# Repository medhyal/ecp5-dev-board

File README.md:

# ecp5-dev-board
ECP5 FPGA DEV BOARD

Lattice LFE5U-12F FPGA  
Built in FTDI FT2232H Programmer

Errata:  
Q1 - wrong footprint

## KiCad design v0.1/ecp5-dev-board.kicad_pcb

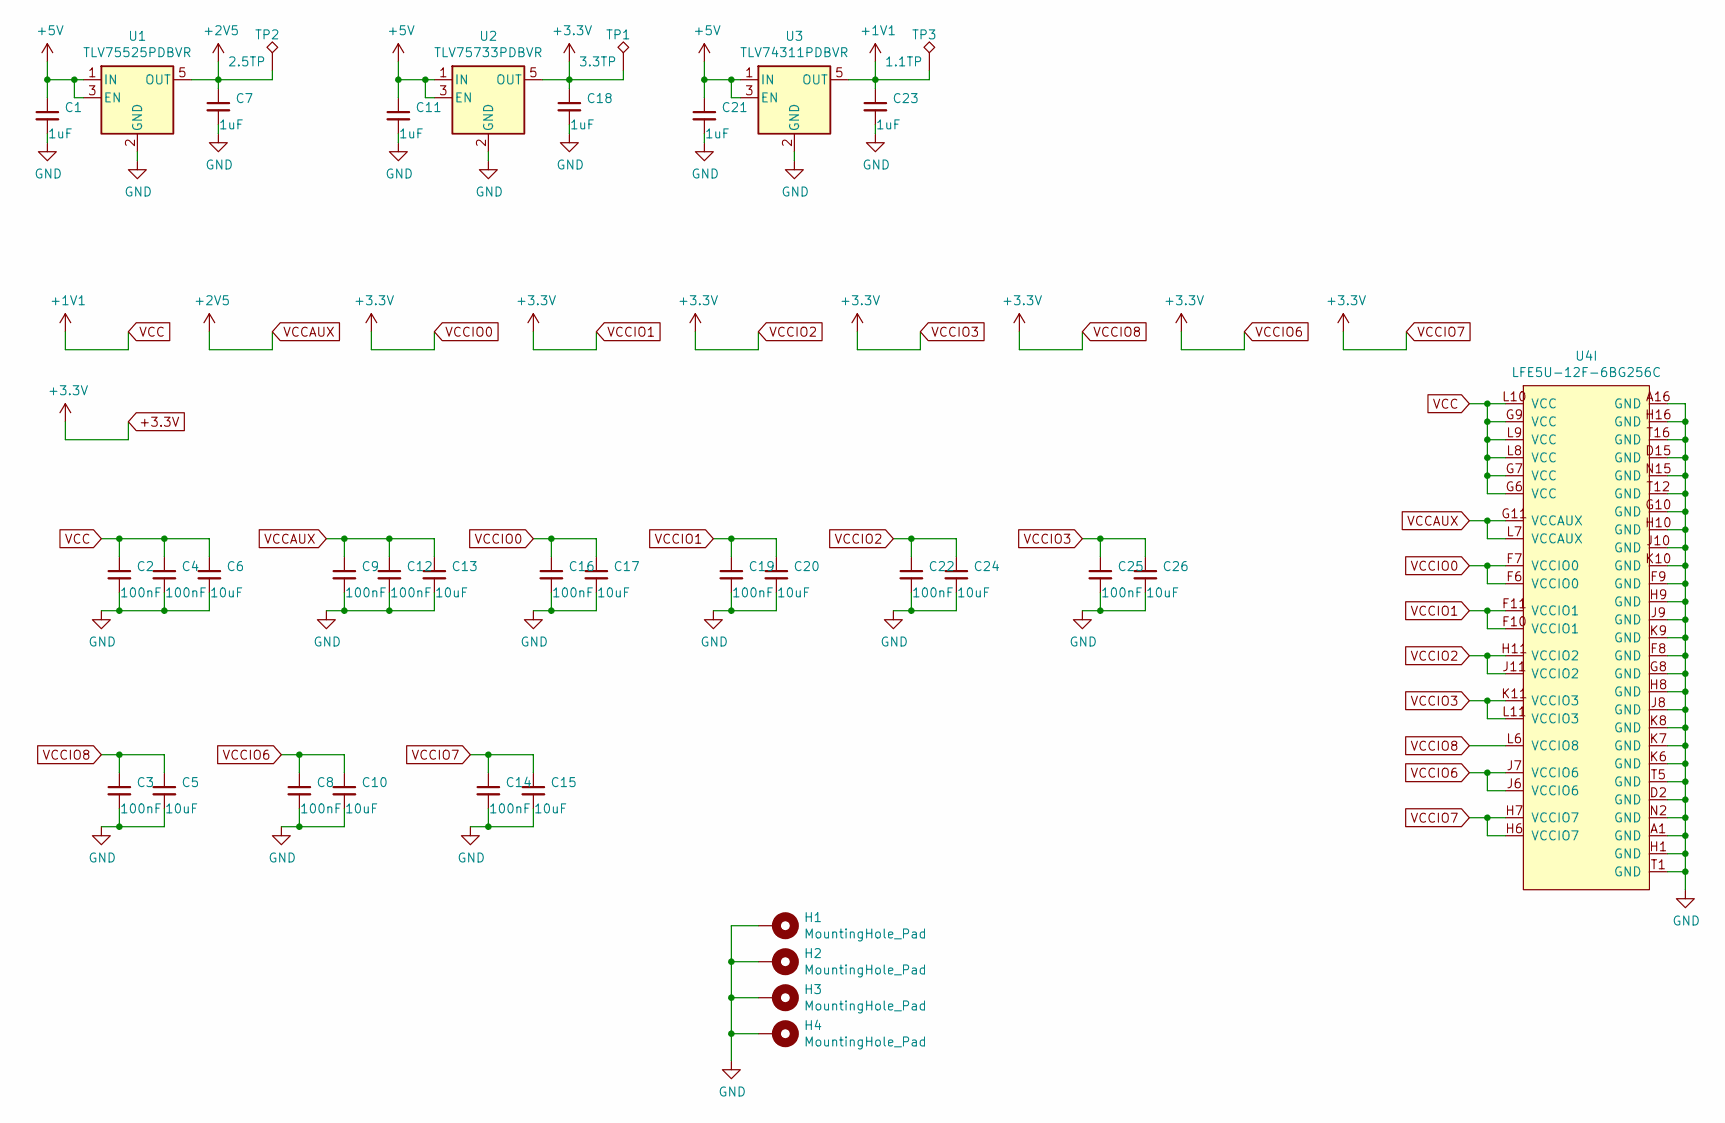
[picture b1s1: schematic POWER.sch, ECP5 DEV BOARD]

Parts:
C1, C7, C11, C18, C21, C23: 1uF; C_0603_1608Metric
C2, C3, C4, C8, C9, C12, C14, C16, C19, C22, C25: 100nF; C_0402_1005Metric
C5, C6, C10, C13, C15, C17, C20, C24, C26: 10uF; C_0402_1005Metric
H1, H2, H3, H4: MountingHole_Pad; MountingHole_3.2mm_M3_ISO14580_Pad
TP1: 3.3TP; TestPoint_Pad_D1.0mm
TP2: 2.5TP; TestPoint_Pad_D1.0mm
TP3: 1.1TP; TestPoint_Pad_D1.0mm
U1: TLV75525PDBVR; SOT-23-5
U2: TLV75733PDBVR; SOT-23-5
U3: TLV74311PDBVR; SOT-23-5
U4: LFE5U-12F-6BG256C; BGA-256_14.0x14.0mm_Layout16x16_P0.8mm_Ball0.45mm_Pad0.32mm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

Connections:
+3.3V: C3.1, C5.1, C8.1, C10.1, C14.1, C15.1, C16.1, C17.1, C18.1, C19.1, C20.1, C22.1, C24.1, C25.1, C26.1, TP1.1, U2.5 (OUT), U4.F6 (VCCIO0), U4.F7 (VCCIO0), U4.F10 (VCCIO1), U4.F11 (VCCIO1), U4.H6 (VCCIO7), U4.H7 (VCCIO7), U4.H11 (VCCIO2), U4.J6 (VCCIO6), U4.J7 (VCCIO6), U4.J11 (VCCIO2), U4.K11 (VCCIO3), U4.L6 (VCCIO8), U4.L11 (VCCIO3); also elsewhere on the board
+5V: C1.1, C11.1, C21.1, U1.1 (IN), U1.3 (EN), U2.1 (IN), U2.3 (EN), U3.1 (IN), U3.3 (EN); also elsewhere on the board
VCC: C2.1, C4.1, C6.1, C23.1, TP3.1, U3.5 (OUT), U4.G6 (VCC), U4.G7 (VCC), U4.G9 (VCC), U4.L8 (VCC), U4.L9 (VCC), U4.L10 (VCC)
VCCAUX: C7.1, C9.1, C12.1, C13.1, TP2.1, U1.5 (OUT), U4.G11 (VCCAUX), U4.L7 (VCCAUX)

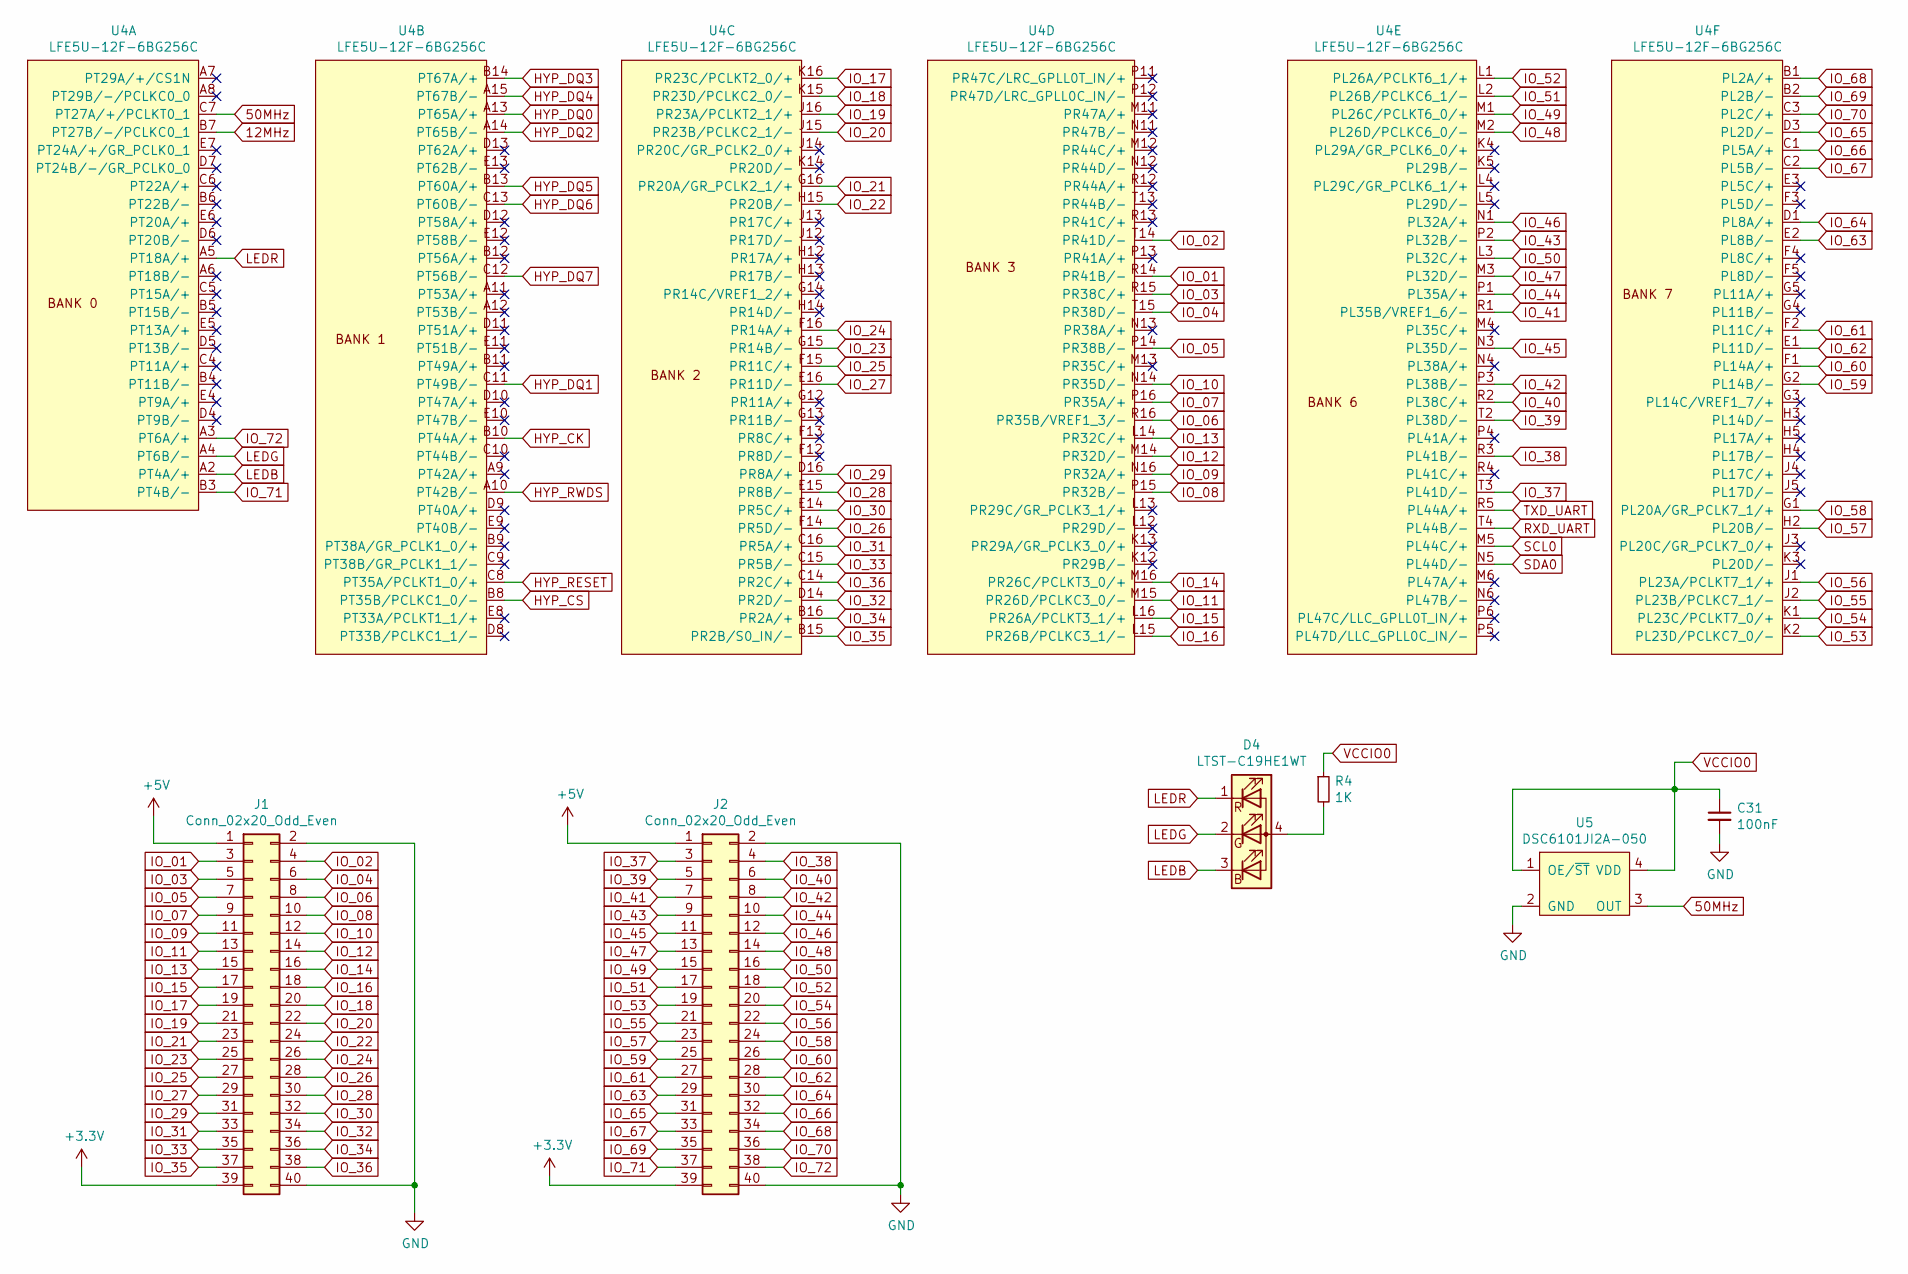
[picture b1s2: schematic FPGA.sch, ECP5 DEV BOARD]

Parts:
C31: 100nF; C_0402_1005Metric
D4: ‎LTST-C19HE1WT‎; LED_LiteOn_LTST-C19HE1WT
J1, J2: Conn_02x20_Odd_Even; PinHeader_2x20_P2.54mm_Vertical
R4: 1K; R_0402_1005Metric
U4: LFE5U-12F-6BG256C; BGA-256_14.0x14.0mm_Layout16x16_P0.8mm_Ball0.45mm_Pad0.32mm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
U5: DSC6101JI2A-050; DSC6101JI2A-012

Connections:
12MHz: U4.B7 (PT27B/-/PCLKC0_1); also elsewhere on the board
50MHz: U4.C7 (PT27A/+/PCLKT0_1), U5.3 (OUT)
+3.3V: C31.1, J1.39, J2.39, R4.1, U5.1 (OE/~ST), U5.4 (VDD); also elsewhere on the board
+5V: J1.1, J2.1; also elsewhere on the board
HYP_CK: U4.B10 (PT44A/+); also elsewhere on the board
HYP_CS: U4.B8 (PT35B/PCLKC1_0/-); also elsewhere on the board
HYP_DQ0: U4.A13 (PT65A/+); also elsewhere on the board
HYP_DQ1: U4.C11 (PT49B/-); also elsewhere on the board
HYP_DQ2: U4.A14 (PT65B/-); also elsewhere on the board
HYP_DQ3: U4.B14 (PT67A/+); also elsewhere on the board
HYP_DQ4: U4.A15 (PT67B/-); also elsewhere on the board
HYP_DQ5: U4.B13 (PT60A/+); also elsewhere on the board
HYP_DQ6: U4.C13 (PT60B/-); also elsewhere on the board
HYP_DQ7: U4.C12 (PT56B/-); also elsewhere on the board
HYP_RESET: U4.C8 (PT35A/PCLKT1_0/+); also elsewhere on the board
HYP_RWDS: U4.A10 (PT42B/-); also elsewhere on the board
IO_01: J1.3, U4.R14 (PR41B/-)
IO_02: J1.4, U4.T14 (PR41D/-)
IO_03: J1.5, U4.R15 (PR38C/+)
IO_04: J1.6, U4.T15 (PR38D/-)
IO_05: J1.7, U4.P14 (PR38B/-)
IO_06: J1.8, U4.R16 (PR35B/VREF1_3/-)
IO_07: J1.9, U4.P16 (PR35A/+)
IO_08: J1.10, U4.P15 (PR32B/-)
IO_09: J1.11, U4.N16 (PR32A/+)
IO_10: J1.12, U4.N14 (PR35D/-)
IO_11: J1.13, U4.M15 (PR26D/PCLKC3_0/-)
IO_12: J1.14, U4.M14 (PR32D/-)
IO_13: J1.15, U4.L14 (PR32C/+)
IO_14: J1.16, U4.M16 (PR26C/PCLKT3_0/+)
IO_15: J1.17, U4.L16 (PR26A/PCLKT3_1/+)
IO_16: J1.18, U4.L15 (PR26B/PCLKC3_1/-)
IO_17: J1.19, U4.K16 (PR23C/PCLKT2_0/+)
IO_18: J1.20, U4.K15 (PR23D/PCLKC2_0/-)
IO_19: J1.21, U4.J16 (PR23A/PCLKT2_1/+)
IO_20: J1.22, U4.J15 (PR23B/PCLKC2_1/-)
IO_21: J1.23, U4.G16 (PR20A/GR_PCLK2_1/+)
IO_22: J1.24, U4.H15 (PR20B/-)
IO_23: J1.25, U4.G15 (PR14B/-)
IO_24: J1.26, U4.F16 (PR14A/+)
IO_25: J1.27, U4.F15 (PR11C/+)
IO_26: J1.28, U4.F14 (PR5D/-)
IO_27: J1.29, U4.E16 (PR11D/-)
IO_28: J1.30, U4.E15 (PR8B/-)
IO_29: J1.31, U4.D16 (PR8A/+)
IO_30: J1.32, U4.E14 (PR5C/+)
IO_31: J1.33, U4.C16 (PR5A/+)
IO_32: J1.34, U4.D14 (PR2D/-)
IO_33: J1.35, U4.C15 (PR5B/-)
IO_34: J1.36, U4.B16 (PR2A/+)
IO_35: J1.37, U4.B15 (PR2B/S0_IN/-)
IO_36: J1.38, U4.C14 (PR2C/+)
IO_37: J2.3, U4.T3 (PL41D/-)
IO_38: J2.4, U4.R3 (PL41B/-)
IO_39: J2.5, U4.T2 (PL38D/-)
IO_40: J2.6, U4.R2 (PL38C/+)
IO_41: J2.7, U4.R1 (PL35B/VREF1_6/-)
IO_42: J2.8, U4.P3 (PL38B/-)
IO_43: J2.9, U4.P2 (PL32B/-)
IO_44: J2.10, U4.P1 (PL35A/+)
IO_45: J2.11, U4.N3 (PL35D/-)
IO_46: J2.12, U4.N1 (PL32A/+)
IO_47: J2.13, U4.M3 (PL32D/-)
IO_48: J2.14, U4.M2 (PL26D/PCLKC6_0/-)
IO_49: J2.15, U4.M1 (PL26C/PCLKT6_0/+)
IO_50: J2.16, U4.L3 (PL32C/+)
IO_51: J2.17, U4.L2 (PL26B/PCLKC6_1/-)
IO_52: J2.18, U4.L1 (PL26A/PCLKT6_1/+)
IO_53: J2.19, U4.K2 (PL23D/PCLKC7_0/-)
IO_54: J2.20, U4.K1 (PL23C/PCLKT7_0/+)
IO_55: J2.21, U4.J2 (PL23B/PCLKC7_1/-)
IO_56: J2.22, U4.J1 (PL23A/PCLKT7_1/+)
IO_57: J2.23, U4.H2 (PL20B/-)
IO_58: J2.24, U4.G1 (PL20A/GR_PCLK7_1/+)
IO_59: J2.25, U4.G2 (PL14B/-)
IO_60: J2.26, U4.F1 (PL14A/+)
IO_61: J2.27, U4.F2 (PL11C/+)
IO_62: J2.28, U4.E1 (PL11D/-)
IO_63: J2.29, U4.E2 (PL8B/-)
IO_64: J2.30, U4.D1 (PL8A/+)
IO_65: J2.31, U4.D3 (PL2D/-)
IO_66: J2.32, U4.C1 (PL5A/+)
IO_67: J2.33, U4.C2 (PL5B/-)
IO_68: J2.34, U4.B1 (PL2A/+)
IO_69: J2.35, U4.B2 (PL2B/-)
IO_70: J2.36, U4.C3 (PL2C/+)
IO_71: J2.37, U4.B3 (PT4B/-)
IO_72: J2.38, U4.A3 (PT6A/+)
LEDB: D4.3 (BK), U4.A2 (PT4A/+)
LEDG: D4.2 (GK), U4.A4 (PT6B/-)
LEDR: D4.1 (RK), U4.A5 (PT18A/+)
unnamed: D4.4 (A), R4.2
RXD_UART: U4.N5 (PL44D/-), U4.T4 (PL44B/-); also elsewhere on the board
SCL0: U4.M5 (PL44C/+), U4.R5 (PL44A/+); also elsewhere on the board

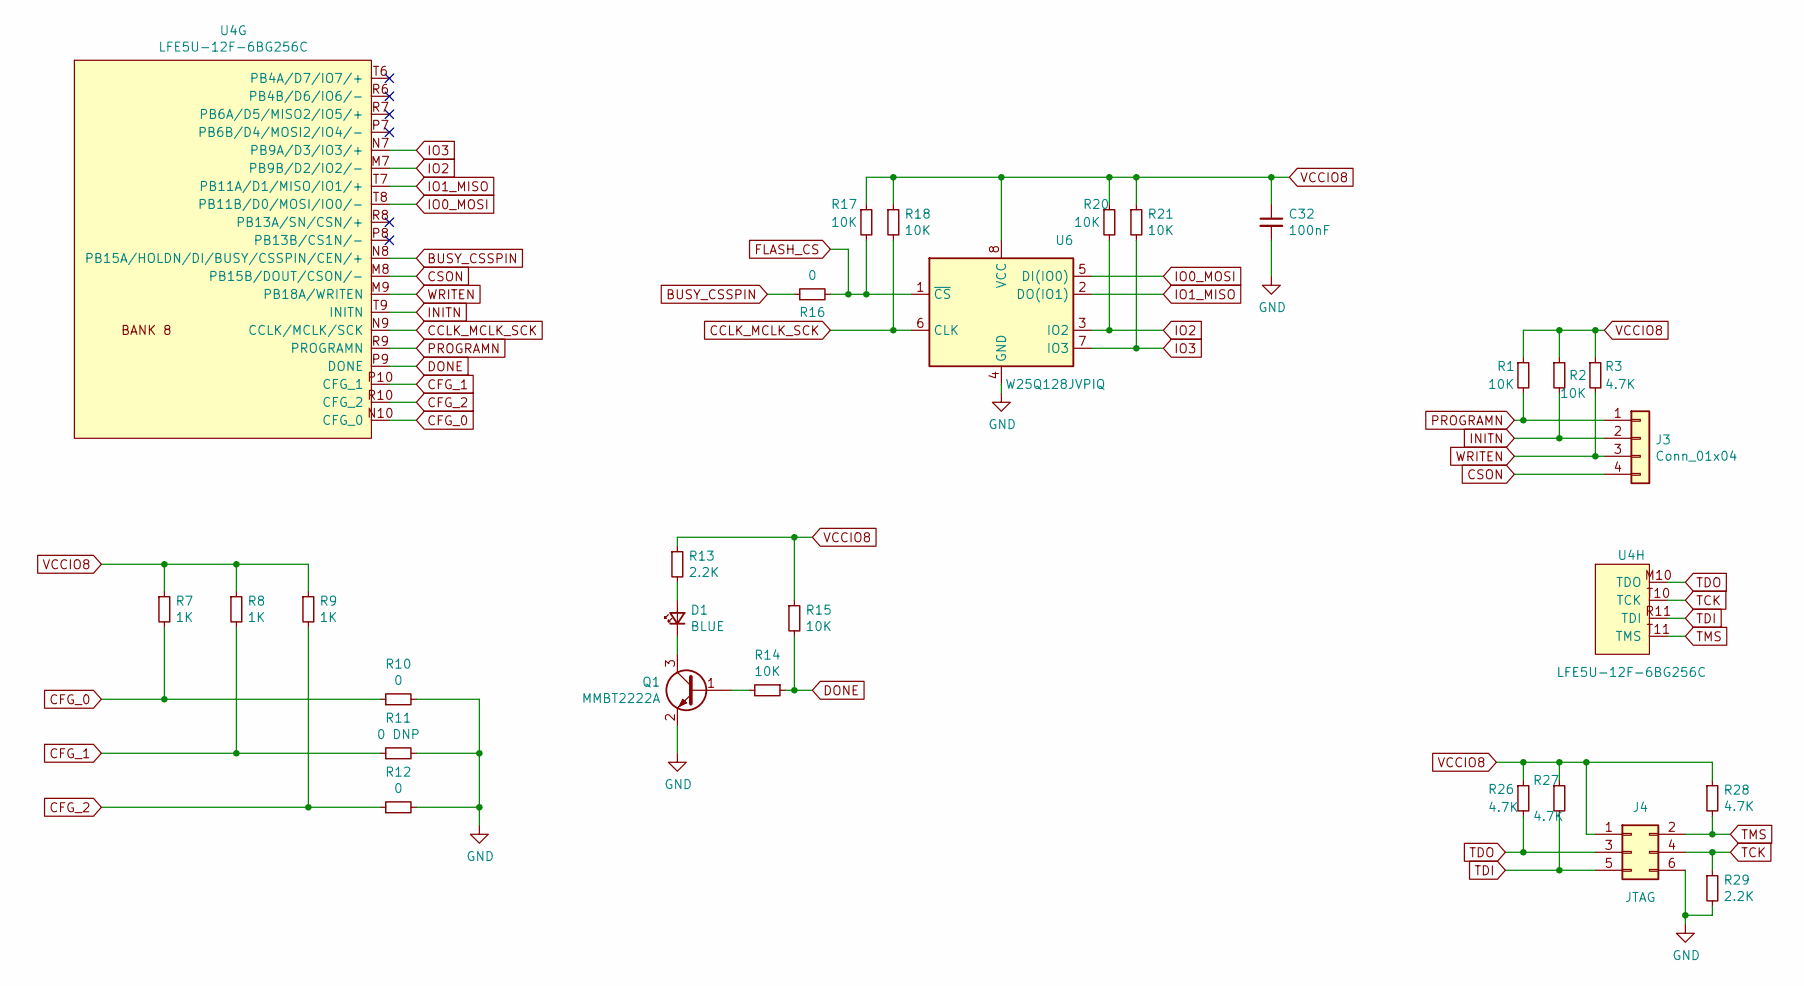
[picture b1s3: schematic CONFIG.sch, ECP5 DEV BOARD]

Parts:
C32: 100nF; C_0402_1005Metric
D1: BLUE; LED_0603_1608Metric
J3: Conn_01x04; PinHeader_1x04_P2.54mm_Vertical
J4: JTAG; PinHeader_2x03_P2.54mm_Vertical
Q1: MMBT2222A; SOT-23
R1, R2, R14, R15, R17, R18, R20, R21: 10K; R_0402_1005Metric
R3, R26, R27, R28: 4.7K; R_0402_1005Metric
R7, R8, R9: 1K; R_0402_1005Metric
R10, R12, R16: 0; R_0402_1005Metric
R11: 0 DNP; R_0402_1005Metric
R13, R29: 2.2K; R_0402_1005Metric
U4: LFE5U-12F-6BG256C; BGA-256_14.0x14.0mm_Layout16x16_P0.8mm_Ball0.45mm_Pad0.32mm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
U6: W25Q128JVPIQ; WSON-8-1EP_6x5mm_P1.27mm_EP3.4x4.3mm

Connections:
+3.3V: C32.1, J4.1, R1.1, R2.1, R3.1, R7.1, R8.1, R9.1, R13.1, R15.1, R17.1, R18.1, R20.1, R21.1, R26.1, R27.1, R28.1, U6.8 (VCC); also elsewhere on the board
BUSY_CSSPIN: R16.1, U4.N8 (PB15A/HOLDN/DI/BUSY/CSSPIN/CEN/+)
CCLK_MCLK_SCK: R18.2, U4.N9 (CCLK/MCLK/SCK), U6.6 (CLK)
CFG_0: R7.2, R10.1, U4.N10 (CFG_0)
CFG_1: R8.2, R11.1, U4.P10 (CFG_1)
CFG_2: R9.2, R12.1, U4.R10 (CFG_2)
CSON: J3.4, U4.M8 (PB15B/DOUT/CSON/-)
DONE: R14.1, R15.2, U4.P9 (DONE)
FLASH_CS: R16.2, R17.2, U6.1 (~CS)
INITN: J3.2, R2.2, U4.T9 (INITN)
IO0_MOSI: U4.T8 (PB11B/D0/MOSI/IO0/-), U6.5 (DI(IO0))
IO1_MISO: U4.T7 (PB11A/D1/MISO/IO1/+), U6.2 (DO(IO1))
IO2: R20.2, U4.M7 (PB9B/D2/IO2/-), U6.3 (IO2)
IO3: R21.2, U4.N7 (PB9A/D3/IO3/+), U6.7 (IO3)
unnamed: D1.1 (K), Q1.3 (C)
unnamed: D1.2 (A), R13.2
PROGRAMN: J3.1, R1.2, U4.R9 (PROGRAMN)
TCK: J4.4, R29.1, U4.T10 (TCK); also elsewhere on the board
TDI: J4.5, R27.2, U4.R11 (TDI); also elsewhere on the board
TDO: J4.3, R26.2, U4.M10 (TDO); also elsewhere on the board
TMS: J4.2, R28.2, U4.T11 (TMS); also elsewhere on the board
WRITEN: J3.3, R3.2, U4.M9 (PB18A/WRITEN)

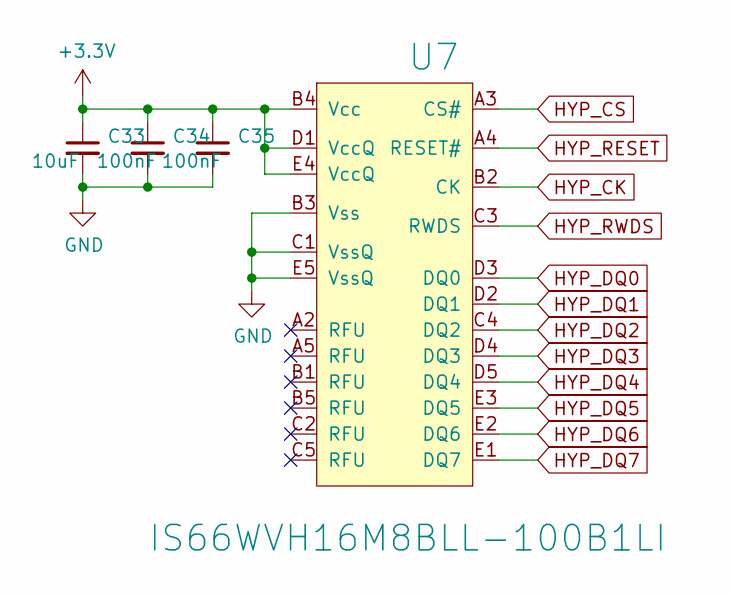
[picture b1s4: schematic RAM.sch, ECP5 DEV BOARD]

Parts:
C33: 10uF; C_0402_1005Metric
C34, C35: 100nF; C_0402_1005Metric
U7: IS66WVH16M8BLL-100B1LI; 24-TFBGA (6x8)

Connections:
+3.3V: C33.1, C34.1, C35.1, U7.B4 (Vcc), U7.D1 (VccQ), U7.E4 (VccQ); also elsewhere on the board
HYP_CK: U7.B2 (CK); also elsewhere on the board
HYP_CS: U7.A3 (CS#); also elsewhere on the board
HYP_DQ0: U7.D3 (DQ0); also elsewhere on the board
HYP_DQ1: U7.D2 (DQ1); also elsewhere on the board
HYP_DQ2: U7.C4 (DQ2); also elsewhere on the board
HYP_DQ3: U7.D4 (DQ3); also elsewhere on the board
HYP_DQ4: U7.D5 (DQ4); also elsewhere on the board
HYP_DQ5: U7.E3 (DQ5); also elsewhere on the board
HYP_DQ6: U7.E2 (DQ6); also elsewhere on the board
HYP_DQ7: U7.E1 (DQ7); also elsewhere on the board
HYP_RESET: U7.A4 (RESET#); also elsewhere on the board
HYP_RWDS: U7.C3 (RWDS); also elsewhere on the board

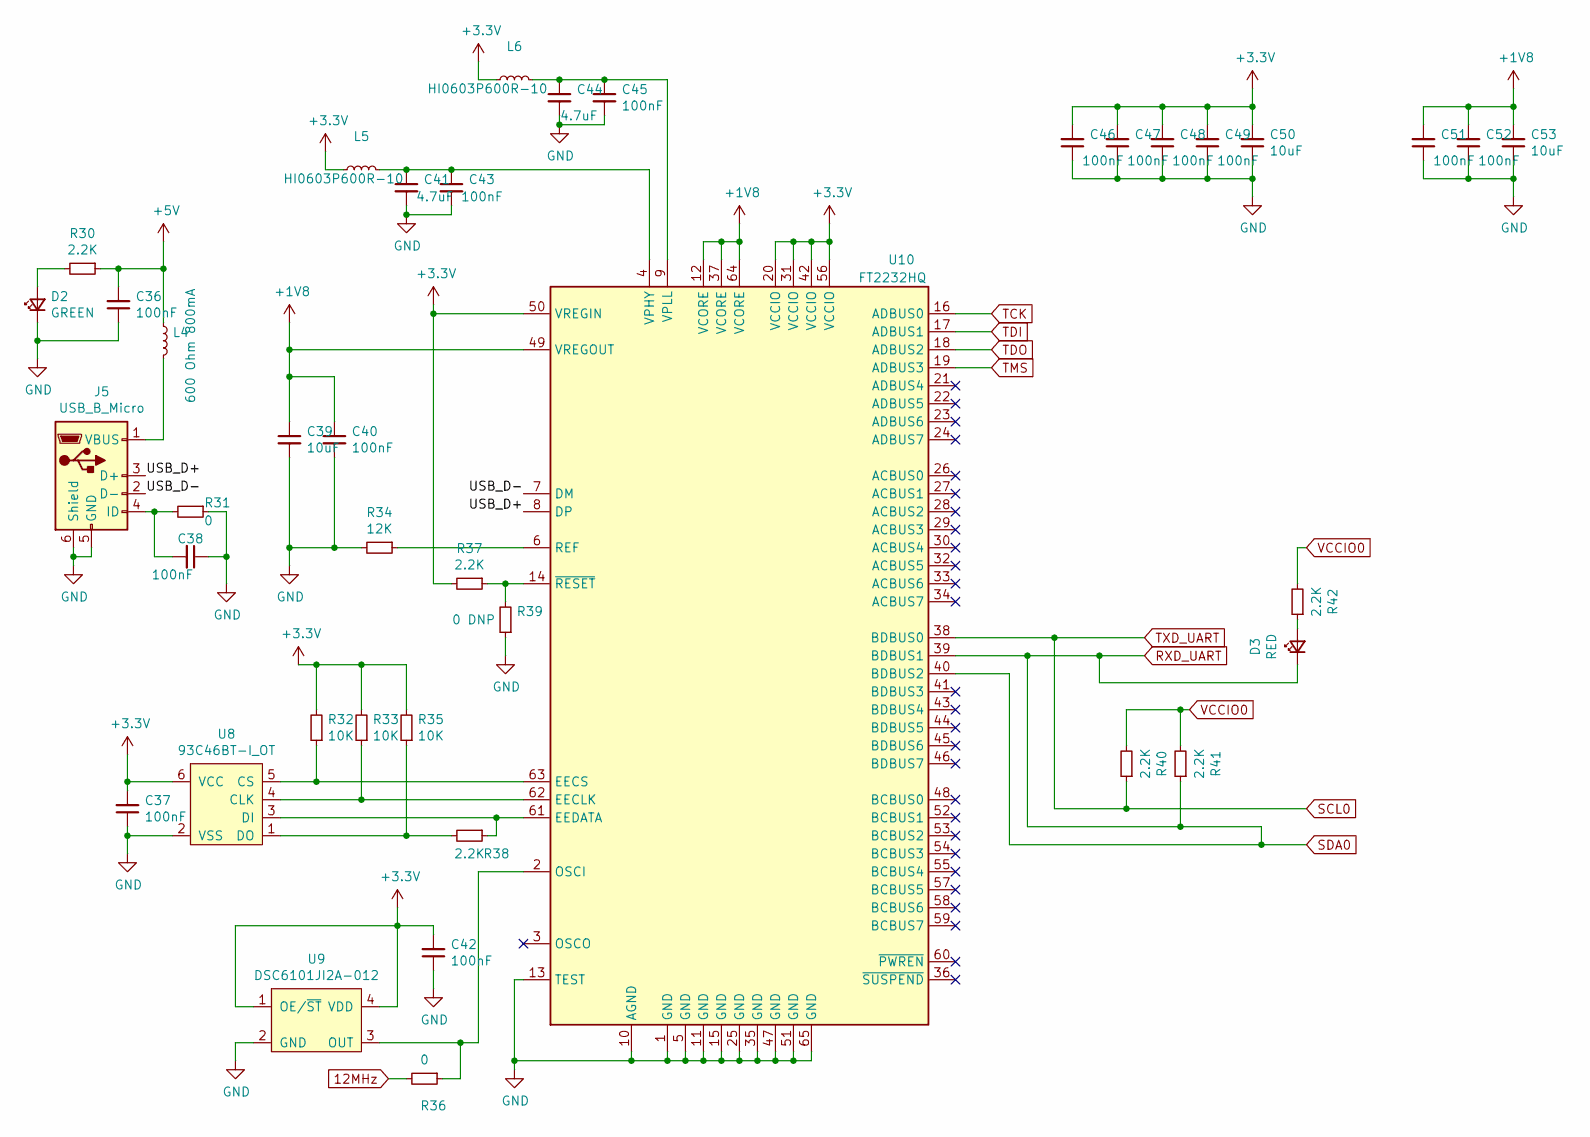
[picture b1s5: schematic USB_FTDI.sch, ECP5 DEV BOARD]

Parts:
C36: 100nF; C_0603_1608Metric
C37, C38, C40, C42, C43, C45, C46, C47, C48, C49, C51, C52: 100nF; C_0402_1005Metric
C39, C50, C53: 10uF; C_0402_1005Metric
C41, C44: 4.7uF; C_0402_1005Metric
D2: GREEN; LED_0603_1608Metric
D3: RED; LED_0603_1608Metric
J5: USB_B_Micro; USB_Micro-B_Molex_47346-0001
L4: 600 Ohm 800mA; L_0603_1608Metric
L5, L6: HI0603P600R-10; L_0603_1608Metric
R30, R37, R38, R40, R41, R42: 2.2K; R_0402_1005Metric
R31, R36: 0; R_0402_1005Metric
R32, R33, R35: 10K; R_0402_1005Metric
R34: 12K; R_0402_1005Metric
R39: 0 DNP; R_0402_1005Metric
U8: 93C46BT-I_OT; SOT-23-6
U9: DSC6101JI2A-012
U10: FT2232HQ; QFN-64-1EP_9x9mm_P0.5mm_EP4.35x4.35mm

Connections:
12MHz: R36.2; also elsewhere on the board
+1V8: C39.1, C40.1, C51.2, C52.2, C53.2, U10.12 (VCORE), U10.37 (VCORE), U10.49 (VREGOUT), U10.64 (VCORE)
+3.3V: C37.2, C42.2, C46.2, C47.2, C48.2, C49.2, C50.2, L5.1, L6.1, R32.2, R33.2, R35.2, R37.2, R40.2, R41.2, R42.2, U8.6 (VCC), U9.1 (OE/~ST), U9.4 (VDD), U10.20 (VCCIO), U10.31 (VCCIO), U10.42 (VCCIO), U10.50 (VREGIN), U10.56 (VCCIO); also elsewhere on the board
+5V: C36.2, L4.1, R30.1; also elsewhere on the board
/USB_FTDI/USB_D+: J5.3 (D+), U10.8 (DP)
/USB_FTDI/USB_D-: J5.2 (D-), U10.7 (DM)
unnamed: C38.2, J5.4 (ID), R31.2
unnamed: C41.1, C43.1, L5.2, U10.4 (VPHY)
unnamed: C44.1, C45.1, L6.2, U10.9 (VPLL)
unnamed: D2.2 (A), R30.2
unnamed: D3.2 (A), R42.1
unnamed: J5.1 (VBUS), L4.2
unnamed: R32.1, U8.5 (CS), U10.63 (EECS)
unnamed: R33.1, U8.4 (CLK), U10.62 (EECLK)
unnamed: R34.1, U10.6 (REF)
unnamed: R35.1, R38.2, U8.1 (DO)
unnamed: R36.1, U9.3 (OUT), U10.2 (OSCI)
unnamed: R37.1, R39.2, U10.14 (~RESET)
unnamed: R38.1, U8.3 (DI), U10.61 (EEDATA)
RXD_UART: D3.1 (K), R41.1, U10.39 (BDBUS1), U10.40 (BDBUS2); also elsewhere on the board
SCL0: R40.1, U10.38 (BDBUS0); also elsewhere on the board
TCK: U10.16 (ADBUS0); also elsewhere on the board
TDI: U10.17 (ADBUS1); also elsewhere on the board
TDO: U10.18 (ADBUS2); also elsewhere on the board
TMS: U10.19 (ADBUS3); also elsewhere on the board

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
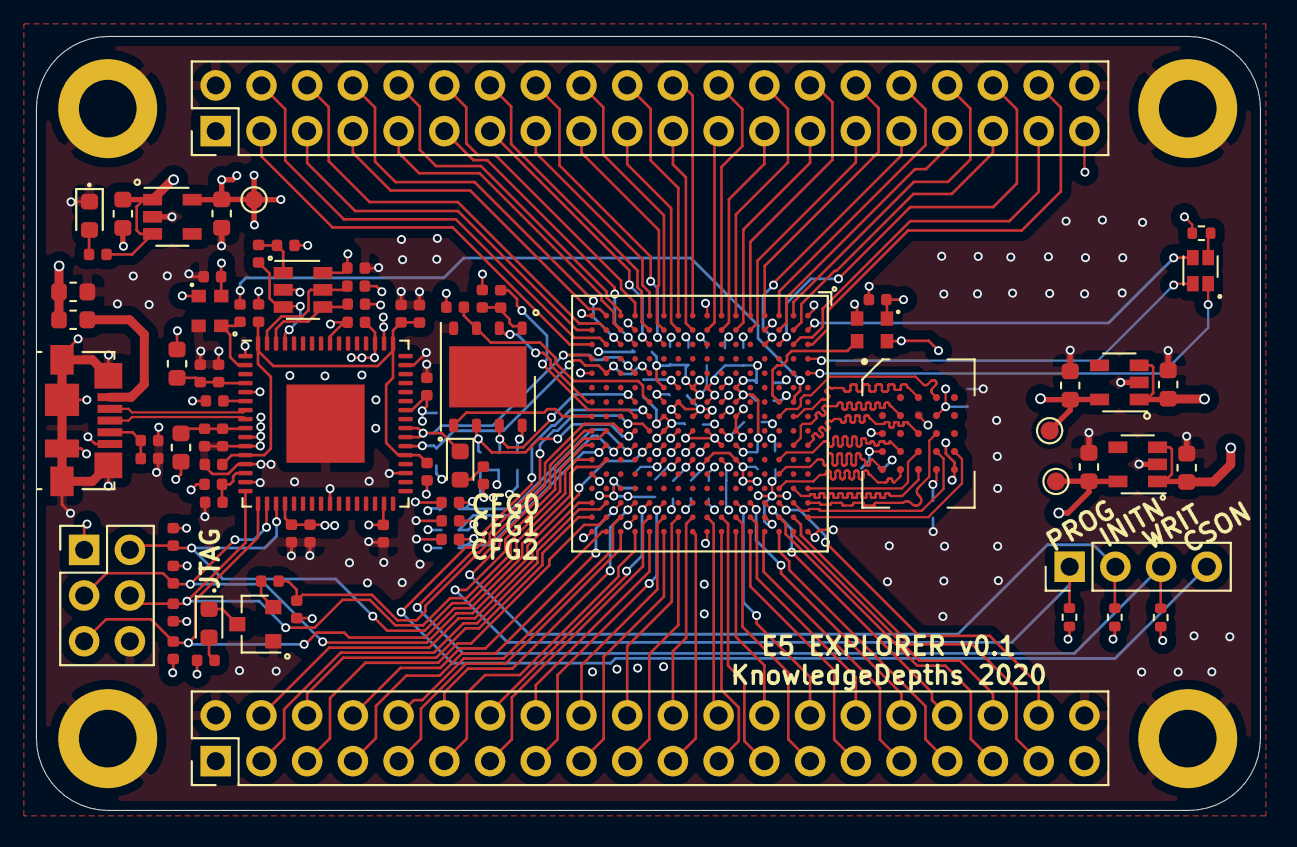
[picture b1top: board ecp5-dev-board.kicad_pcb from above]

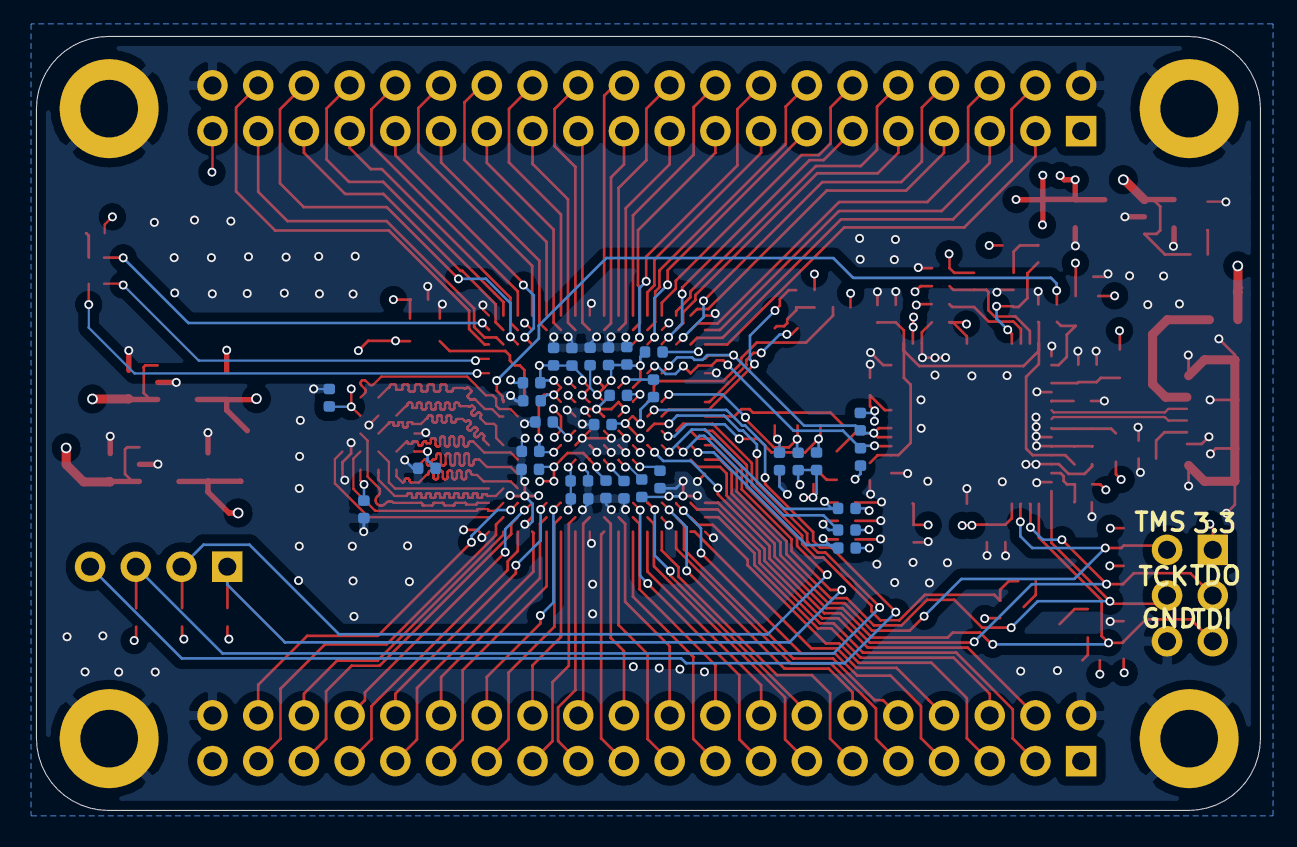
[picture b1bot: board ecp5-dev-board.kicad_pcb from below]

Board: 4 copper layers, 68.0 x 43.0 mm, 114 parts (31 on the bottom side), 135 nets.

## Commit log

2021-04-18 Initial Commits
